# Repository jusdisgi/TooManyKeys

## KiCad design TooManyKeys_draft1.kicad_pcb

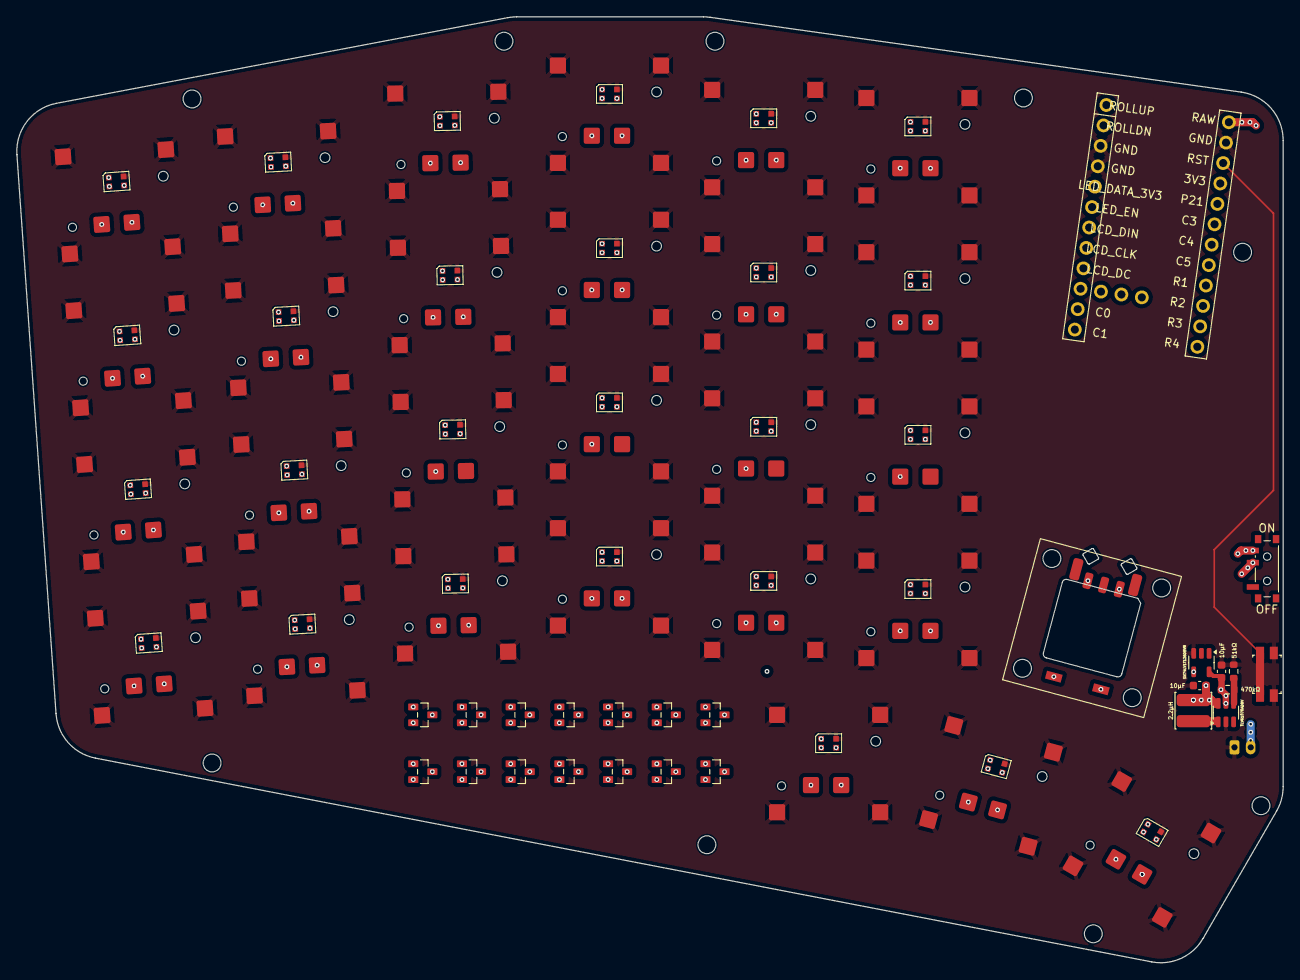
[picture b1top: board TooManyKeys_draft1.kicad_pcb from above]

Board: 6 copper layers, 156.0 x 116.5 mm, 89 parts (1 on the bottom side), 70 nets.

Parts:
C1, C2: 10μF; C_0603_1608Metric
D1, D2, D3, D4, D5, D6, D7, D8, D9, D10, D11, D12, D13, D14: BAV70; BAV70 SOT23
JST1: battery_connector_jst_ph_2
L1: 2.2μH; L_CJIANG_FTC404030S_4.1x4.1x3.0_SMD
LED1, LED2, LED3, LED4, LED5, LED6, LED7, LED8, LED9, LED10, LED11, LED12, LED13, LED14, LED15, LED16, LED17, LED18, LED19, LED20, LED21, LED22, LED23, LED24, LED25, LED26, LED27: LED_WS2812B-2020_PLCC4_2.0x2.0mm
MCU1: mcu_nice_nano
MH1, MH2, MH3, MH4, MH5, MH6, MH7, MH8, MH9: mounting_hole_npth
PWR1: power_switch_smd_side
R1: 470kΩ; R_0603_1608Metric
R2: 51kΩ; R_0603_1608Metric
RE1: CKW12
RST1: reset_switch_smd_side
S1, S2, S3, S4, S5, S6, S7, S8, S9, S10, S11, S12, S13, S14, S15, S16, S17, S18, S19, S20, S21, S22, S23, S24, S25, S26, S27: PG1316S
U1: TLV61070ADBV; SOT-23-6
U2: SN74LV1T126DBVR; SOT-23-5

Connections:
BAT_P: JST1.2, PWR1.3
BOOST_EN: U1.3 (EN), U2.1
C0: MCU1.14, S1.1, S2.1, S3.1, S4.1
C1: MCU1.13, S5.1, S6.1, S7.1, S8.1
C2: MCU1.27, S9.1, S10.1, S11.1, S12.1, S25.1
C3: MCU1.6, S13.1, S14.1, S15.1, S16.1, S26.1
C4: MCU1.7, S17.1, S18.1, S19.1, S20.1, S27.1
C5: MCU1.8, RE1.S1, S21.1, S22.1, S23.1, S24.1
GND: C1.2, C2.2, JST1.1, LED1.4, LED2.4, LED3.4, LED4.4, LED5.4, LED6.4, LED7.4, LED8.4, LED9.4, LED10.4, LED11.4, LED12.4, LED13.4, LED14.4, LED15.4, LED16.4, LED17.4, LED18.4, LED19.4, LED20.4, LED21.4, LED22.4, LED23.4, LED24.4, LED25.4, LED26.4, LED27.4, MCU1.2, MCU1.21, MCU1.22, R2.2, RE1.B, RST1.1, RST1.3, S1.3, S2.3, S3.3, S4.3, S5.3, S6.3, S7.3, S8.3, S9.3, S10.3, S11.3, S12.3, S13.3, S14.3, S15.3, S16.3, S17.3, S18.3, S19.3, S20.3, S21.3, S22.3, S23.3, S24.3, S25.3, S26.3, S27.3, U1.2 (GND), U2.3 (GND)
LED_1: LED26.1, LED27.3
LED_2: LED25.1, LED26.3
LED_3: LED21.1, LED25.3
LED_4: LED21.3, LED22.1
LED_5: LED22.3, LED23.1
LED_6: LED23.3, LED24.1
LED_7: LED20.1, LED24.3
LED_8: LED19.1, LED20.3
LED_9: LED18.1, LED19.3
LED_10: LED17.1, LED18.3
LED_11: LED13.1, LED17.3
LED_12: LED13.3, LED14.1
LED_13: LED14.3, LED15.1
LED_14: LED15.3, LED16.1
LED_15: LED12.1, LED16.3
LED_16: LED11.1, LED12.3
LED_17: LED10.1, LED11.3
LED_18: LED9.1, LED10.3
LED_19: LED5.1, LED9.3
LED_20: LED5.3, LED6.1
LED_21: LED6.3, LED7.1
LED_22: LED7.3, LED8.1
LED_23: LED4.1, LED8.3
LED_24: LED3.1, LED4.3
LED_25: LED2.1, LED3.3
LED_26: LED1.1, LED2.3
LED_DATA_3V3: MCU1.20, U2.2
LED_DATA_5V: LED27.1, U2.4
LED_PWR: C2.1, LED1.2, LED2.2, LED3.2, LED4.2, LED5.2, LED6.2, LED7.2, LED8.2, LED9.2, LED10.2, LED11.2, LED12.2, LED13.2, LED14.2, LED15.2, LED16.2, LED17.2, LED18.2, LED19.2, LED20.2, LED21.2, LED22.2, LED23.2, LED24.2, LED25.2, LED26.2, LED27.2, R1.1, U1.5 (V_{OUT}), U2.5 (VCC)
unnamed: L1.2, U1.1 (SW)
unnamed: R1.2, R2.1, U1.4 (V_{FB})
R1: D1.3, D2.3, D3.3, D4.3, D5.3, D6.3, D7.3, D8.3, D9.3, D10.3, D11.3, D12.3, D13.3, D14.3, MCU1.9
RAW: C1.1, L1.1, MCU1.1, PWR1.2, U1.6 (V_{IN})
ROLLDN: MCU1.23, RE1.C
ROLLUP: MCU1.24, RE1.A
RST: MCU1.3, RST1.2, RST1.4
finger_index_bottom: D12.1, S17.2
finger_index_home: D9.1, S18.2
finger_index_num: D3.1, S20.2
finger_index_top: D6.1, S19.2
finger_inner_bottom: D12.2, S21.2
finger_inner_home: D9.2, S22.2
finger_inner_num: D3.2, S24.2
finger_inner_top: D6.2, S23.2
finger_middle_bottom: D11.2, S13.2
finger_middle_home: D8.2, S14.2
finger_middle_num: D2.2, S16.2
finger_middle_top: D5.2, S15.2
finger_outer_bottom: D10.1, D10.2, S1.2
finger_outer_home: D7.1, D7.2, S2.2
finger_outer_num: D1.1, S4.2
finger_outer_top: D4.1, D4.2, S3.2
finger_pinky_num: D1.2, S8.2
finger_ring_bottom: D11.1, S9.2
finger_ring_home: D8.1, S10.2
finger_ring_num: D2.1, S12.2
finger_ring_top: D5.1, S11.2
roller: D14.2, RE1.S2
thumb_far_fan: D14.1, S27.2
thumb_mid_fan: D13.2, S26.2
thumb_near_fan: D13.1, S25.2

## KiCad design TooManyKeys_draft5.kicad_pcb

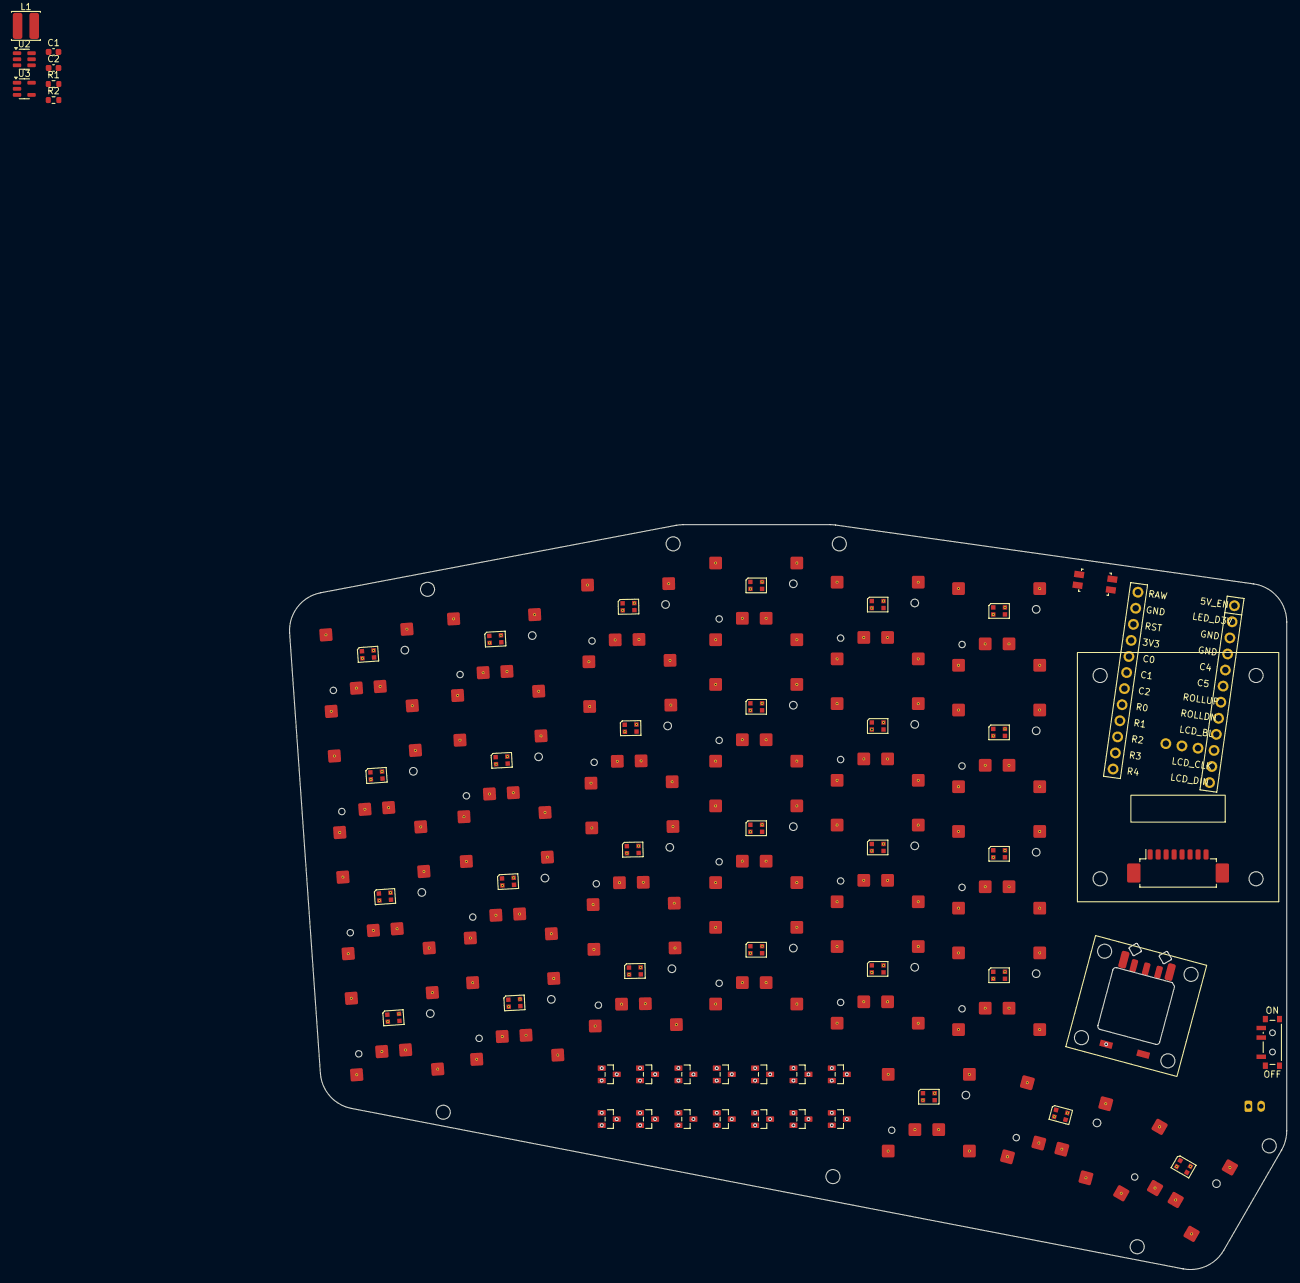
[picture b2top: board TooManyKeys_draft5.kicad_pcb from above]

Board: 6 copper layers, 156.0 x 116.5 mm, 89 parts (1 on the bottom side), 83 nets.

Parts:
C1, C2: 10μF; C_0603_1608Metric
CONN1: Molex_PicoBlade_53261-0871_1x08-1MP_P1.25mm_Horizontal
D1, D2, D3, D4, D5, D6, D7, D8, D9, D10, D11, D12, D13, D14: BAV70; BAV70 SOT23
JST1: battery_connector_jst_ph_2
L1: 2.2μH; L_CJIANG_FTC404030S_4.1x4.1x3.0_SMD
LCD1: LCD_1.69_Waveshare
LED1, LED2, LED3, LED4, LED5, LED6, LED7, LED8, LED9, LED10, LED11, LED12, LED13, LED14, LED15, LED16, LED17, LED18, LED19, LED20, LED21, LED22, LED23, LED24, LED25, LED26, LED27: LED_WS2812B-2020_PLCC4_2.0x2.0mm
MCU1: mcu_nice_nano
MH1, MH2, MH3, MH4, MH5, MH6, MH7: mounting_hole_npth
PWR1: power_switch_smd_side
R1: 470kΩ; R_0603_1608Metric
R2: 51kΩ; R_0603_1608Metric
RE1: CKW12
RST1: reset_switch_smd_side
S1, S2, S3, S4, S5, S6, S7, S8, S9, S10, S11, S12, S13, S14, S15, S16, S17, S18, S19, S20, S21, S22, S23, S24, S25, S26, S27: PG1316S
U2: TLV61070ADBV; SOT-23-6
U3: SN74LV1T126DBVR; SOT-23-5

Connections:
3V3: CONN1.1, MCU1.21 (3.3v)
5V: C2.1, LED1.4 (VDD), LED2.4 (VDD), LED3.4 (VDD), LED4.4 (VDD), LED5.4 (VDD), LED6.4 (VDD), LED7.4 (VDD), LED8.4 (VDD), LED9.4 (VDD), LED10.4 (VDD), LED11.4 (VDD), LED12.4 (VDD), LED13.4 (VDD), LED14.4 (VDD), LED15.4 (VDD), LED16.4 (VDD), LED17.4 (VDD), LED18.4 (VDD), LED19.4 (VDD), LED20.4 (VDD), LED21.4 (VDD), LED22.4 (VDD), LED23.4 (VDD), LED24.4 (VDD), LED25.4 (VDD), LED26.4 (VDD), LED27.4 (VDD), R1.1, U2.5 (V_{OUT}), U3.5 (VCC)
5V_EN: MCU1.1, U2.3 (EN), U3.1
BAT_P: JST1.2, PWR1.2 (B)
BOOST_FB: R1.2, R2.1, U2.4 (V_{FB})
BOOST_SW: L1.2, U2.1 (SW)
C0: MCU1.20 (21), S1.1, S2.1, S3.1, S4.1
C1: MCU1.19 (20), S5.2, S6.2, S7.2, S8.2
C2: MCU1.18 (19), S9.1, S10.1, S11.1, S12.1, S25.1
C3: MCU1.27 (7), S13.2, S14.2, S15.2, S16.2, S26.2
C4: MCU1.5 (2), S17.1, S18.1, S19.1, S20.1, S27.1
C5: MCU1.6 (3), RE1.S1, S21.2, S22.2, S23.2, S24.2
GND: C1.2, C2.2, CONN1.2, JST1.1, LED1.2 (VSS), LED2.2 (VSS), LED3.2 (VSS), LED4.2 (VSS), LED5.2 (VSS), LED6.2 (VSS), LED7.2 (VSS), LED8.2 (VSS), LED9.2 (VSS), LED10.2 (VSS), LED11.2 (VSS), LED12.2 (VSS), LED13.2 (VSS), LED14.2 (VSS), LED15.2 (VSS), LED16.2 (VSS), LED17.2 (VSS), LED18.2 (VSS), LED19.2 (VSS), LED20.2 (VSS), LED21.2 (VSS), LED22.2 (VSS), LED23.2 (VSS), LED24.2 (VSS), LED25.2 (VSS), LED26.2 (VSS), LED27.2 (VSS), MCU1.3 (GND), MCU1.4 (GND), MCU1.23 (GND), R2.2, RE1.B, RST1.1, RST1.3, U2.2 (GND), U3.3 (GND)
LCD_BL: CONN1.8, MCU1.9 (6)
LCD_CLK: CONN1.4, MCU1.11 (8)
LCD_CS: CONN1.5, MCU1.26 (2)
LCD_DC: CONN1.6, MCU1.10 (7)
LCD_DIN: CONN1.3, MCU1.12 (9)
LCD_RST: CONN1.7, MCU1.25 (1)
LED_D3V: MCU1.2 (0), U3.2
LED_D5V: LED27.3 (DIN), U3.4
unnamed: D1.1 (A), S4.2
unnamed: D1.2 (A), S8.1
unnamed: D2.1 (A), S12.2
unnamed: D2.2 (A), S16.1
unnamed: D3.1 (A), S20.2
unnamed: D3.2 (A), S24.1
unnamed: D4.1 (A), S3.2
unnamed: D4.2 (A), S7.1
unnamed: D5.1 (A), S11.2
unnamed: D5.2 (A), S15.1
unnamed: D6.1 (A), S19.2
unnamed: D6.2 (A), S23.1
unnamed: D7.1 (A), S2.2
unnamed: D7.2 (A), S6.1
unnamed: D8.1 (A), S10.2
unnamed: D8.2 (A), S14.1
unnamed: D9.1 (A), S18.2
unnamed: D9.2 (A), S22.1
unnamed: D10.1 (A), S1.2
unnamed: D10.2 (A), S5.1
unnamed: D11.1 (A), S9.2
unnamed: D11.2 (A), S13.1
unnamed: D12.1 (A), S17.2
unnamed: D12.2 (A), S21.1
unnamed: D13.1 (A), S27.2
unnamed: D14.1 (A), S25.2
unnamed: D14.2 (A), S26.1
unnamed: LED1.3 (DIN), LED2.1 (DOUT)
unnamed: LED2.3 (DIN), LED3.1 (DOUT)
unnamed: LED3.3 (DIN), LED4.1 (DOUT)
unnamed: LED4.3 (DIN), LED8.1 (DOUT)
unnamed: LED5.3 (DIN), LED9.1 (DOUT)
unnamed: LED5.1 (DOUT), LED6.3 (DIN)
unnamed: LED6.1 (DOUT), LED7.3 (DIN)
unnamed: LED7.1 (DOUT), LED8.3 (DIN)
unnamed: LED10.3 (DIN), LED11.1 (DOUT)
unnamed: LED9.3 (DIN), LED10.1 (DOUT)
unnamed: LED11.3 (DIN), LED12.1 (DOUT)
unnamed: LED12.3 (DIN), LED16.1 (DOUT)
unnamed: LED13.3 (DIN), LED17.1 (DOUT)
unnamed: LED13.1 (DOUT), LED14.3 (DIN)
unnamed: LED14.1 (DOUT), LED15.3 (DIN)
unnamed: LED15.1 (DOUT), LED16.3 (DIN)
unnamed: LED17.3 (DIN), LED18.1 (DOUT)
unnamed: LED18.3 (DIN), LED19.1 (DOUT)
unnamed: LED19.3 (DIN), LED20.1 (DOUT)
unnamed: LED20.3 (DIN), LED24.1 (DOUT)
unnamed: LED21.3 (DIN), LED25.1 (DOUT)
unnamed: LED21.1 (DOUT), LED22.3 (DIN)
unnamed: LED22.1 (DOUT), LED23.3 (DIN)
unnamed: LED23.1 (DOUT), LED24.3 (DIN)
unnamed: LED25.3 (DIN), LED26.1 (DOUT)
unnamed: LED26.3 (DIN), LED27.1 (DOUT)
unnamed: MCU1.22 (RST), RST1.2, RST1.4
R0: D1.3 (K), D2.3 (K), D3.3 (K), MCU1.17 (18)
R1: D4.3 (K), D5.3 (K), D6.3 (K), MCU1.16 (15)
R2: D7.3 (K), D8.3 (K), D9.3 (K), MCU1.15 (14)
R3: D10.3 (K), D11.3 (K), D12.3 (K), MCU1.14 (16)
R4: D13.3 (K), D14.3 (K), MCU1.13 (10)
RAW: C1.1, L1.1, MCU1.24 (B+), PWR1.1 (A), U2.6 (V_{IN})
ROLLDN: MCU1.8 (5), RE1.C
ROLLUP: MCU1.7 (4), RE1.A
